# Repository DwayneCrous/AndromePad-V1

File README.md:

# AndromePad V1

A custom mechanical macropad PCB project by DwayneR Engineering, designed in KiCad. This is the first revision of the macropad.

## Features

*   Powered by a Seeeduino XIAO series microcontroller.
*   Includes a rotary encoder with a switch, which can be used for volume control, scrolling, or other functions.
*   Uses a TCA9555RTWR 16-bit I/O expander to manage the key matrix.
*   Includes a potentiometer.
*   Designed with components from the Seeed Studio OPL KiCad library.

## Key Components

*   Seeeduino XIAO microcontroller
*   TCA9555RTWR 16-bit I/O expander
*   Rotary Encoder with switch
*   Potentiometer
*   Mechanical keyswitches
*   Diodes, Resistors, and Capacitors

## Software

This project is designed using [KiCad](https://www.kicad.org/), an open-source EDA software. You will need to have KiCad installed to view and edit the project files.

## How to Use

1.  Clone or download this repository.
2.  Open KiCad.
3.  Go to `File > Open Project...`
4.  Navigate to the `AndromePad V1` directory and open the `AndromePad V1.kicad_pro` file.

## Libraries

This project includes the [OPL_Kicad_Library](https://github.com/Seeed-Studio/OPL_Kicad_Library) from Seeed Studio. The library is included in the `OPL_Kicad_Library-master` directory.

## Bill of Materials (BOM)

To generate the Bill of Materials (BOM):

1.  Open the `AndromePad V1.kicad_sch` file in KiCad's Eeschema.
2.  Go to `Tools > Generate Bill of Materials...`.
3.  You can use the default `bom_csv_grouped_by_value` script or a custom one.

## PCB Layout

<!-- TODO: Replace with an actual image of the PCB layout -->
*(Image of the PCB layout will be here)*

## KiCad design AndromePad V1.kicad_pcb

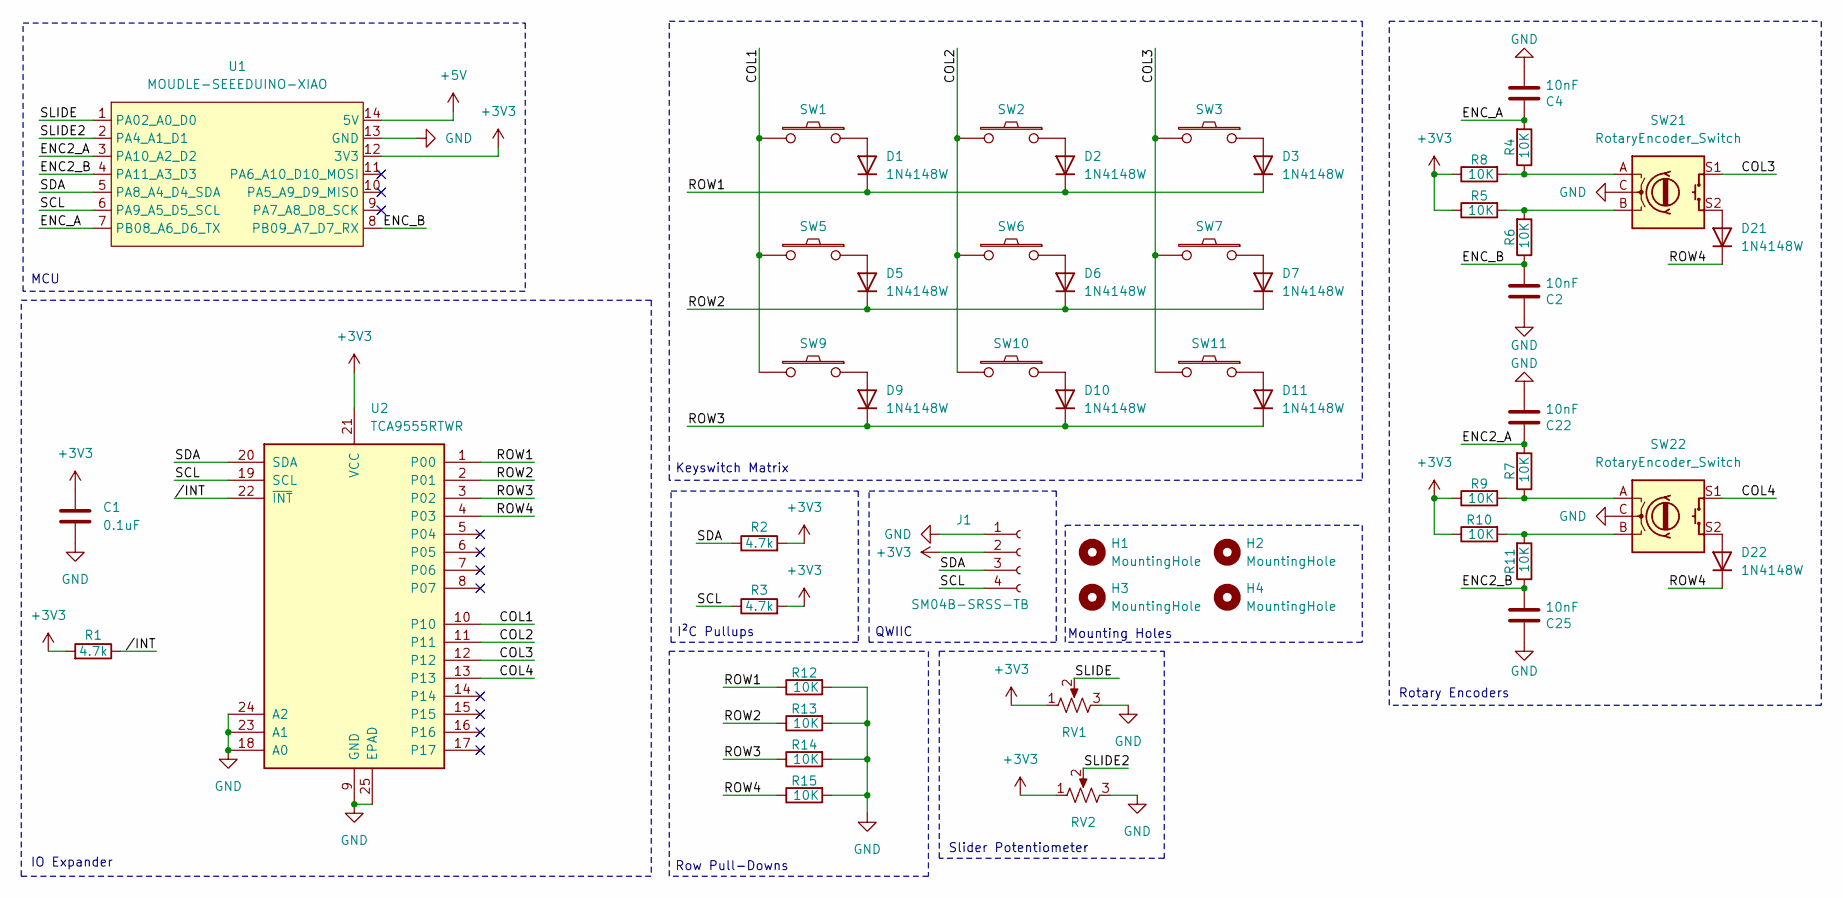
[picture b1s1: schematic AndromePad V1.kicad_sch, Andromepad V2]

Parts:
C1: 0.1uF; C_0603_1608Metric_Pad1.08x0.95mm_HandSolder; DigiKey Part Number CC0603KRX7R7BB104
C2, C4, C22, C25: 10nF; C_0603_1608Metric_Pad1.08x0.95mm_HandSolder; DigiKey Part Number C1608X7R2A103M080AA
D1, D2, D3, D5, D6, D7, D9, D10, D11, D21, D22: 1N4148W; D_SOD-123; DigiKey Part Number 1N4148W
H1, H2, H3, H4: MountingHole; MountingHole_2.2mm_M2
J1: SM04B-SRSS-TB; CONN_SM04B-SRSS-TB_JST; DigiKey Part Number SM04B-SRSS-TB
R1, R2, R3: 4.7k; R_0603_1608Metric_Pad0.98x0.95mm_HandSolder; DigiKey Part Number RMCF0603FT4K70
R4, R5, R6, R7, R8, R9, R10, R11, R12, R13, R14, R15: 10K; R_0603_1608Metric_Pad0.98x0.95mm_HandSolder; DigiKey Part Number RMCF0603FT10K0
RV1, RV2: R_Potentiometer_US; PTA6043-2010CIB103; DigiKey Part Number PTA6043-2010CIB103
SW1, SW2, SW3, SW5, SW6, SW7, SW9, SW10, SW11: keyswitch; SW_Cherry_MX_1.00u_PCB; DigiKey Part Number MX2A-11NA
SW21, SW22: RotaryEncoder_Switch; RotaryEncoder_Alps_EC11E-Switch_Vertical_H20mm; DigiKey Part Number PEC11L-4115F-S0020
U1: MOUDLE-SEEEDUINO-XIAO; XIAO-RP2040-SMD; DigiKey Part Number 1597-102010428-ND
U2: TCA9555RTWR; WQFN-24-1EP_4x4mm_P0.5mm_EP2.45x2.45mm; DigiKey Part Number TCA9555RTWR

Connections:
+3V3: C1.1, J1.2, R1.2, R2.2, R3.2, R5.1, R8.1, R9.1, R10.1, RV1.1, RV2.1, U1.12 (3V3), U2.21 (VCC)
+5V: U1.14 (5V)
/COL1: SW1.2, SW5.2, SW9.2, U2.10
/COL2: SW2.2, SW6.2, SW10.2, U2.11
/COL3: SW3.2, SW7.2, SW11.2, SW21.S1, U2.12
/COL4: SW22.S1, U2.13
/ENC2_A: C22.2, R7.2, U1.3 (PA10_A2_D2)
/ENC2_B: C25.1, R11.1, U1.4 (PA11_A3_D3)
/ENC_A: C4.2, R4.2, U1.7 (PB08_A6_D6_TX)
/ENC_B: C2.1, R6.1, U1.8 (PB09_A7_D7_RX)
/ROW1: D1.1 (K), D2.1 (K), D3.1 (K), R12.1, U2.1 (P00)
/ROW2: D5.1 (K), D6.1 (K), D7.1 (K), R13.1, U2.2 (P01)
/ROW3: D9.1 (K), D10.1 (K), D11.1 (K), R14.1, U2.3 (P02)
/ROW4: D21.1 (K), D22.1 (K), R15.1, U2.4 (P03)
/SCL: J1.4, R3.1, U1.6 (PA9_A5_D5_SCL), U2.19 (SCL)
/SDA: J1.3, R2.1, U1.5 (PA8_A4_D4_SDA), U2.20 (SDA)
/SLIDE: RV1.2, U1.1 (PA02_A0_D0)
/SLIDE2: RV2.2, U1.2 (PA4_A1_D1)
//INT: R1.1, U2.22 (~INT)
GND: C1.2, C2.2, C4.1, C22.1, C25.2, J1.1, R12.2, R13.2, R14.2, R15.2, RV1.3, RV2.3, SW21.C, SW22.C, U1.13 (GND), U2.9 (GND), U2.18 (A0), U2.23 (A1), U2.24 (A2), U2.25 (EPAD)
unnamed: D1.2 (A), SW1.1
unnamed: D2.2 (A), SW2.1
unnamed: D3.2 (A), SW3.1
unnamed: D5.2 (A), SW5.1
unnamed: D6.2 (A), SW6.1
unnamed: D7.2 (A), SW7.1
unnamed: D9.2 (A), SW9.1
unnamed: D10.2 (A), SW10.1
unnamed: D11.2 (A), SW11.1
unnamed: D21.2 (A), SW21.S2
unnamed: D22.2 (A), SW22.S2
unnamed: R4.1, R8.2, SW21.A
unnamed: R5.2, R6.2, SW21.B
unnamed: R7.1, R9.2, SW22.A
unnamed: R10.2, R11.2, SW22.B

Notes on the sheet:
MCU
I²C Pullups
Row Pull-Downs
QWIIC
Mounting Holes
IO Expander
Slider Potentiometer
Rotary Encoders
Keyswitch Matrix

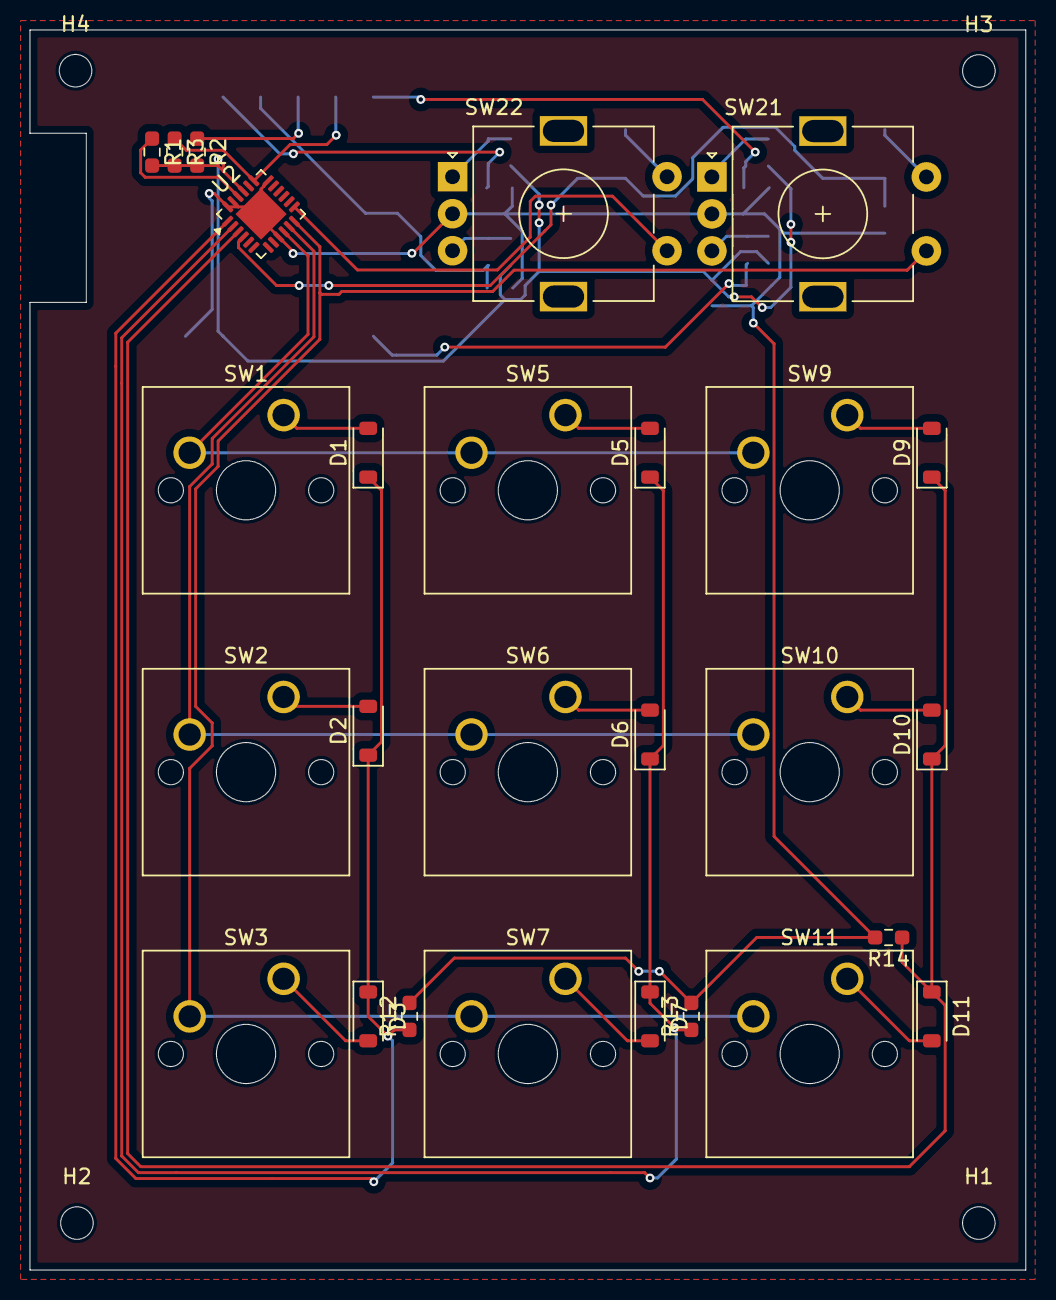
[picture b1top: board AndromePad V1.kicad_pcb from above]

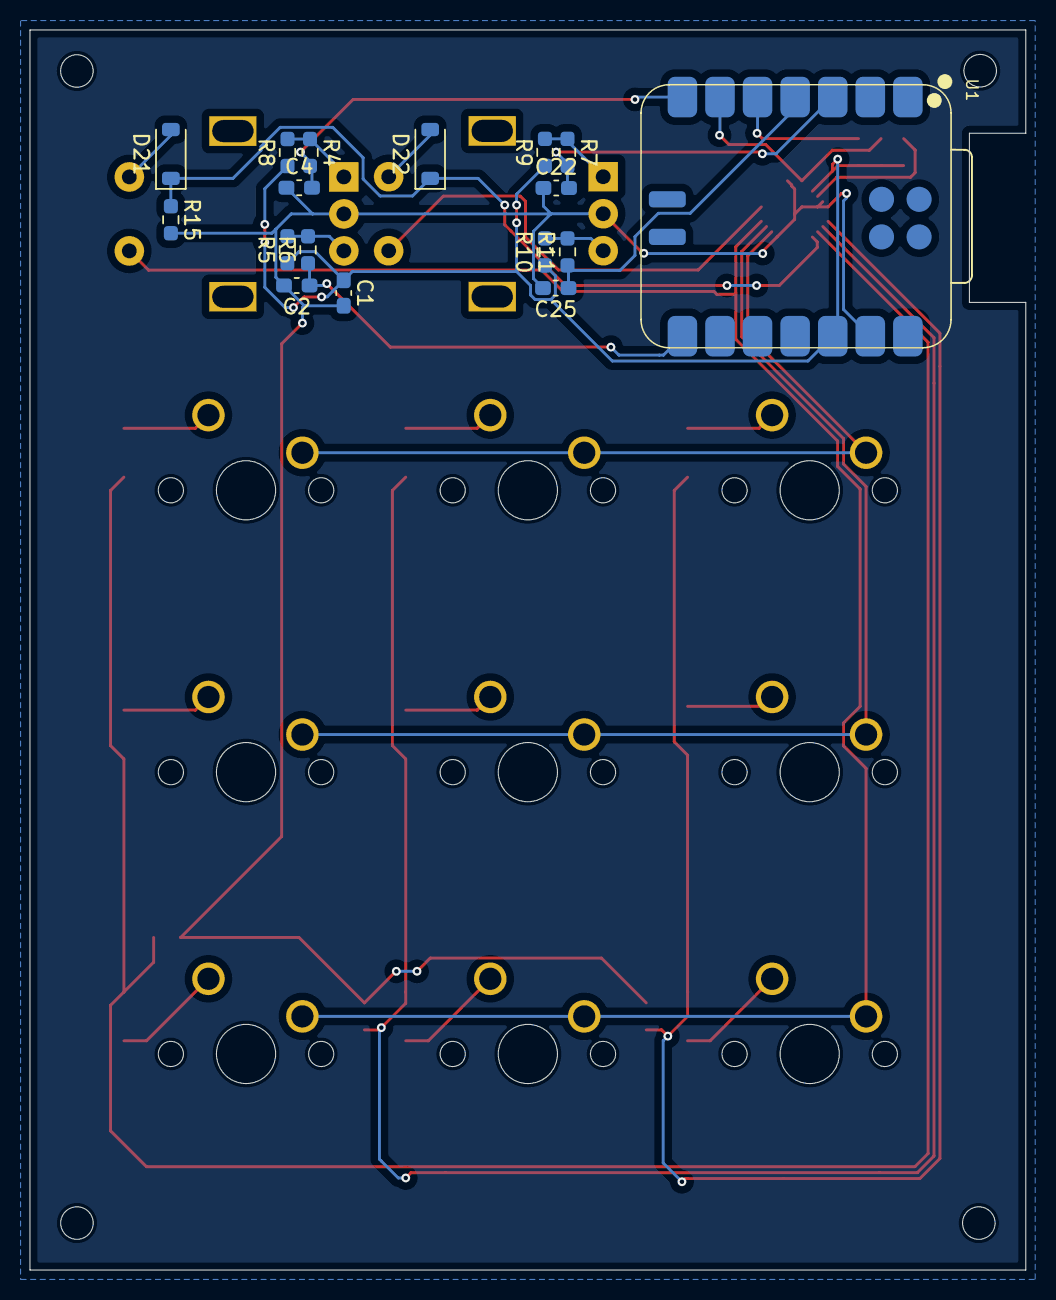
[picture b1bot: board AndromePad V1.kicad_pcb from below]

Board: 2 copper layers, 67.3 x 83.8 mm, 48 parts (17 on the bottom side), 32 nets.

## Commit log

2025-12-04 init
2025-12-04 finished default hackpad tutorial
2025-12-05 completed schematic, still have to work out errors and assign proper footprints
2025-12-05 docs: Add detailed README and .gitignore
2025-12-05 docs: Add PCB layout image and BOM instructions
2025-12-05 build: Ignore images directory and add .gitkeep
2025-12-05 Added Readme.md
2025-12-06 feat: started routing traces in pcb editor, still have to find footprints for sliders
2025-12-07 finished routing in the pcb editor
2025-12-10 feat: updated layout in pcb editor (much cleaner layout and better routing than before)
2025-12-11 feat: added 3d models to footprints in kicad
